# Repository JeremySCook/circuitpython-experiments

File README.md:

# circuitpython-experiments
Experiments with CircuitPython

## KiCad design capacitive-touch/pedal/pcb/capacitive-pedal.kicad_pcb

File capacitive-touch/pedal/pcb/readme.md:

PCB approximately as ordered in ~ March 2023

Could use a few improvements. Included for reference.

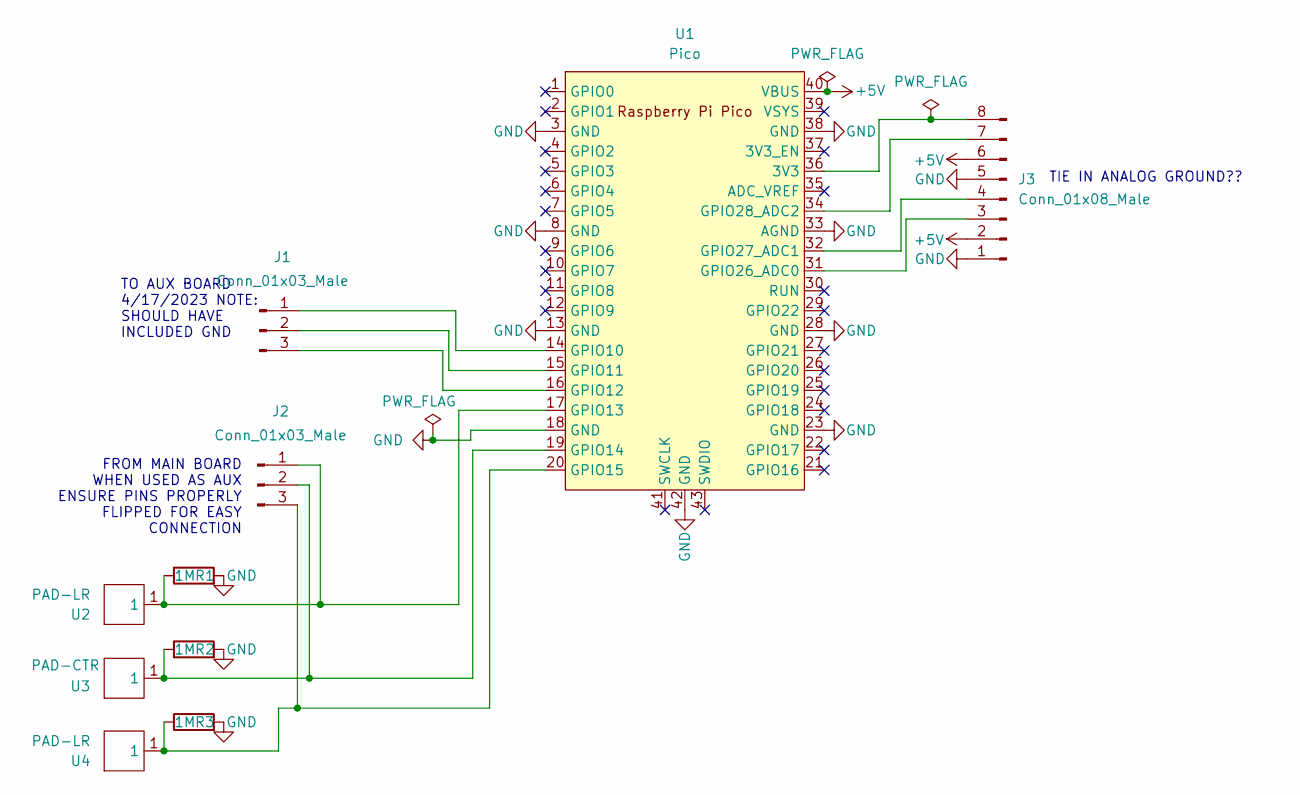
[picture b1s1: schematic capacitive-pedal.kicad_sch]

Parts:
J1, J2: Conn_01x03_Male; PinHeader_1x03_P2.54mm_Vertical
J3: Conn_01x08_Male; PinHeader_1x08_P2.54mm_Vertical
R1, R2, R3: 1M; R_0805_2012Metric_Pad1.20x1.40mm_HandSolder-THT-JSC
U1: Pico; RPi_Pico_SMD_TH
U2, U4: PAD-LR; pad-lr
U3: PAD-CTR; pad-ctr

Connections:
+5V: J3.2, J3.6, U1.40 (VBUS)
GND: J3.1, J3.5, R1.2, R2.2, R3.2, U1.3 (GND), U1.8 (GND), U1.13 (GND), U1.18 (GND), U1.23 (GND), U1.28 (GND), U1.33 (AGND), U1.38 (GND), U1.42 (GND)
unnamed: J3.8, U1.36 (3V3)
unnamed: J1.1, U1.14 (GPIO10)
unnamed: J1.2, U1.15 (GPIO11)
unnamed: J1.3, U1.16 (GPIO12)
unnamed: J2.1, R1.1, U1.17 (GPIO13), U2.1
unnamed: J2.2, R2.1, U1.19 (GPIO14), U3.1
unnamed: J2.3, R3.1, U1.20 (GPIO15), U4.1
unnamed: J3.3, U1.31 (GPIO26_ADC0)
unnamed: J3.4, U1.32 (GPIO27_ADC1)
unnamed: J3.7, U1.34 (GPIO28_ADC2)

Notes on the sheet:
TO AUX BOARD 4/17/2023 NOTE: SHOULD HAVE INCLUDED GND
FROM MAIN BOARD WHEN USED AS AUX ENSURE PINS PROPERLY FLIPPED FOR EASY CONNECTION
TIE IN ANALOG GROUND??

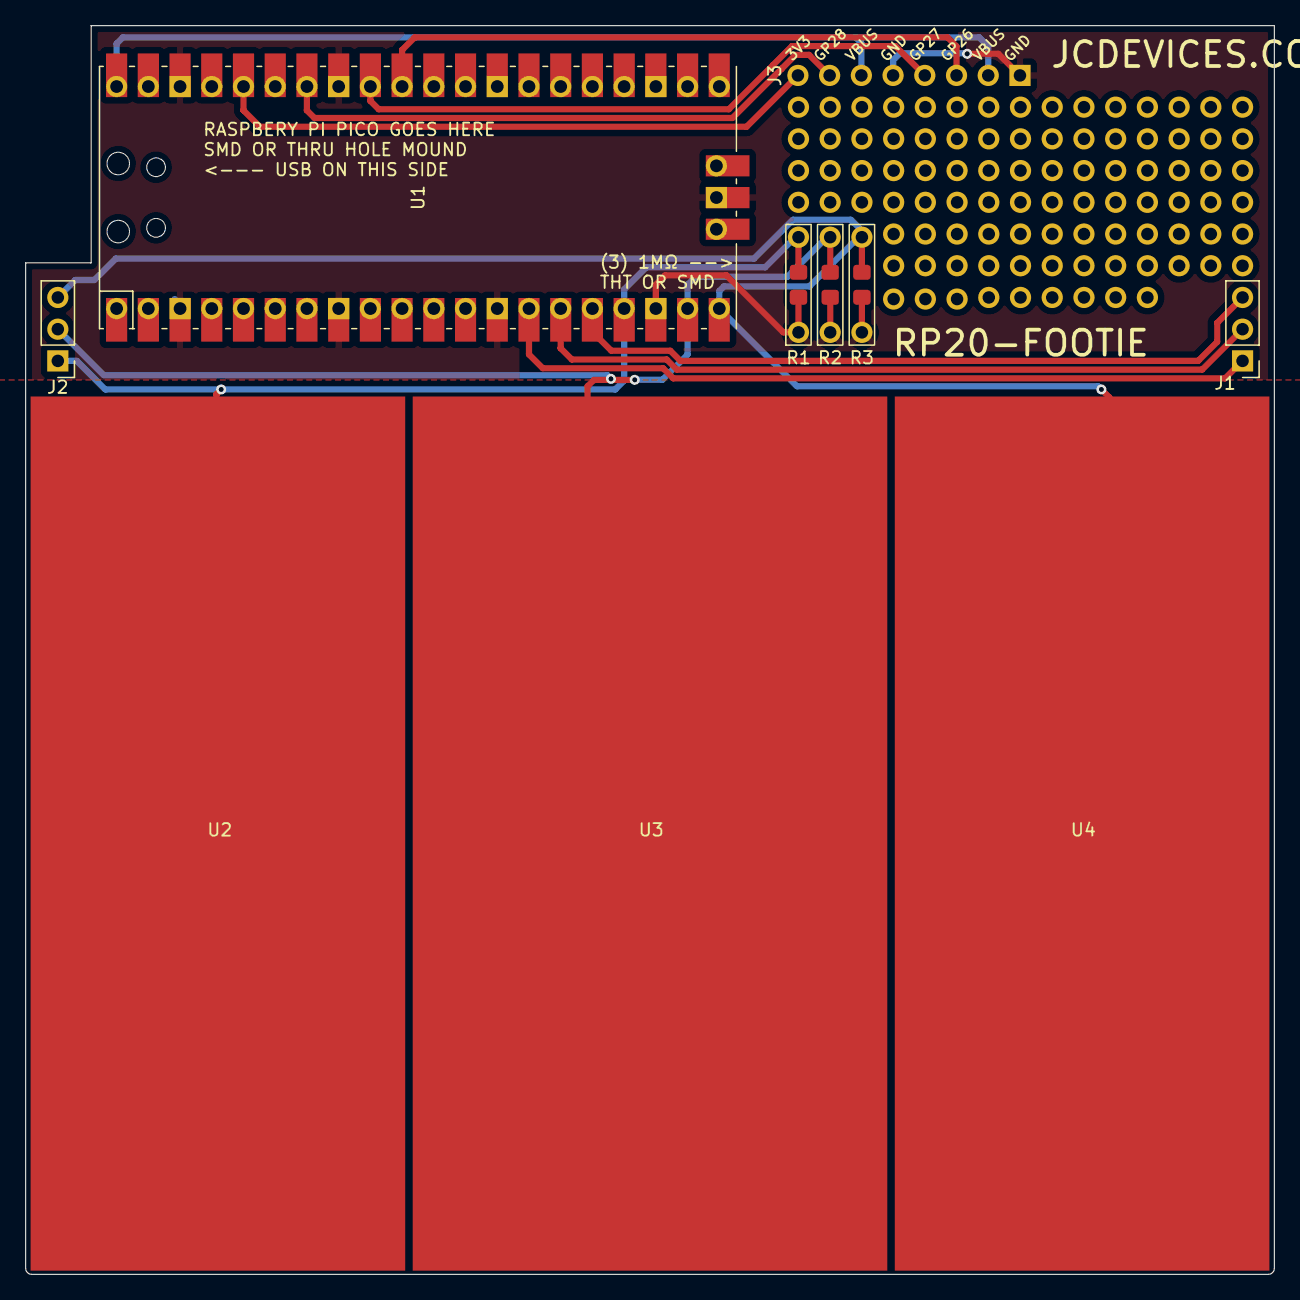
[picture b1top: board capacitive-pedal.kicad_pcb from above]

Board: 2 copper layers, 100.0 x 100.0 mm, 10 parts (0 on the bottom side), 12 nets.

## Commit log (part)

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2023-01-13 Rename RP2040-type-letter.py to Pico-type-letter.py
2023-04-07 Rename tri-pedal.py to tri-pedal-MIDI.py
2023-06-09 Create LICENSE
2023-09-21 Rename RP2040CANBusFeatherListen.py to RP2040CANBusFeatherListenen.py
